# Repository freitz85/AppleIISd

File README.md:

# AppleIISd

SD card based ProFile replacement for enhanced Apple IIe and IIgs computers

The **AppleIISd** is a SD card based replaced for the ProFile harddrive. In contrast to other SD card based devices, this card does not replace a Disk II drive. Data is saved directly onto the SD card, not via images on a FAT system, like on other cards. The SD card is accessable with [CiderPress](http://a2ciderpress.com/).

A Xilinx CPLD is used as a SPI controller and translates, together with the ROM driver, SD card data to/from the Apple IIe. The VHDL source is based on [SPI65/B](http://www.6502.org/users/andre/spi65b) by André Fachat.

The assembler sources are written for CC65. The [schematics](Binary/AppleIISd.pdf) are available as PDF.

## Features

* works with ProDOS and GS/OS
* up to 128MB storage space (4x 65535 blocks)
* ProDOS and Smartport driver in ROM
* Firmware update from ProDOS
* Auto boot
* Access LED
* Card detect and write protect sensing
* Skip boot when Open-Apple key is pressed

## Requirements

The AppleIISd requires an enhanced IIe or IIgs computer. The ROM code uses some 65c02 opcodes and will therefore not work on a II, II+ or unenhanced IIe. It has been tested in the following combinations:

* Apple IIgs Rom 01, GS/OS 6.0.4
* Apple IIgs Rom 01, Prodos 2.4.1
* Apple IIgs Rom 01, Prodos 1.9
* Apple IIe enhanced, 128k, Prodos 2.4.1
* Apple IIe enhanced, 128k, Prodos 1.9
* Apple IIe enhanced, 64k, Prodos 1.9

## Binary distribution

The following files in [Binary/](Binary) have been provided to eliminate the need to compile assembler or VHDL sources.

| File | Purpose |
| ---- | ------- |
| AppleIISd_xx44.jed | CPLD bitfiles for PC44 and VQ44 formfactors |
| AppleIISd.bin | 2k Firmware binary for EPROM |
| AppleIISd.hex | Same as above in INTEL-HEX format |
| AppleIISd.bom.txt | BOM for the board |
| AppleIISd.pdf | Schematic and layout |
| Flasher.bin | Flasher program ProDOS binary |
| Flasher.dsk | Complete ProDOS disk image with Flasher.bin and AppleIISd.bin |
| Gerber_Vx.x.zip | Gerber files for different hw revisions |

## Smartport drive remapping

The AppleIISd features Smartport drivers in ROM to provide more than two drives in both GS/OS and ProDOS.

As ProDOS supports only two drives per slot, additional drives on a Smartport device are mapped to 'phantom slots'. Version prior to version 2 supported only the remapping of drives when the card was in slot 5. Starting with version 2, the remapping seems to work on all slots. The following list shows the assignments as slot/drive, when no other devices are attached:

* Slot 7: 7/1, 7/2, 4/1, 4/2
* Slot 6: 6/1, 6/2, 4/1, 4/1
* Slot 5: 5/1, 5/2, 2/1, 2/1
* Slot 4: 4/1, 4/2, 1/1, 1/2
* Slot 3: 80 col HW, not usable
* Slot 2: 2/1, 2/2, 4/1, 4/2
* Slot 1: 1/1, 1/2, 4/1, 4/2

When more devices are connected, things get a little confusing ;-)

## Building the sources

Be sure to have the newest version of CC65 (V2.16) and some kind of Make instaled, then type one of the following comands:

```bash
make                            # generate binaries
make OPTIONS=mapfile,listing    # generate mapfile and listing, too
make clean                      # delete binaries
```

Alternatively use the VisualStudio solution.

## Timing

The clock of the SPI bus *SCK* may be derived from either *Phi0* or the *7M* clock. Additionally, the divisor may be 2 to 8.

The following measurements were taken with the divisor set to 2, resulting in *fSCK* of 500kHz and 3.5MHz. Reading of a byte requires that a dummy byte is sent on the bus, before the answer can be read. Therefore the measurement is the time between sending the byte and receiving the answer. The measurement for reading of a whole 512 byte block includes the SD card commands to do so.

| Clock  | Byte   | Block  | Image                                             |
| -----: | -----: | -----: | ------------------------------------------------: |
| *Phi0* | 17.7µs | 28.8ms | [Byte](Images/Bus1.gif), [Block](Images/Spi1.png) |
| *7M*   | 3.9µs  | 15ms   | [Byte](Images/Bus2.gif), [Block](Images/Spi2.png) |

This shows that the required to read a single byte can be reduced significantly by increasing *fSCK* (as one might have guessed). Reading at 500kHz actualy requires NOPs to be inserted (or checking the TC bit in the STATUS register), while reading at 3.5MHz can be done immediately.

The time for reading a 512 byte block could *only* be halved, but there are for sure opportunities for optimization in the code surrounding the reading.

```asm
* single byte @ 500kHz
LDA #$FF
STA $C0C0
NOP
NOP
NOP
NOP
NOP
NOP
NOP
LDA $C0C0

* single byte @ 3.5MHz
LDA #$FF
STA $C0C0
LDA $C0C0
```

## Registers

The control registers of the *AppleIISd* are mapped to the usual I/O space at **$C0n0 - $C0n3**, where n is slot+8. All registers and bits are read/write, except where noted.

| Address | Function        | Default value |
| ------- | --------------- | ------------- |
| $C0n0   | DATA            | - |
| $C0n1   | **0:** PGMEN<br>**1:** -<br>**2:** ECE<br>**3:** -<br>**4:** FRX<br>**5:** BSY (R)<br>**6:** -<br>**7:** TC (R) | 0<br>0<br>0<br>0<br>0<br>0<br>0<br>0<br> |
| $C0n2   | unused          | $00 |
| $C0n3   | **0:** /SS<br>**1:** -<br>**2:** -<br>**3:** -<br>**4:** SDHC<br>**5:** WP (R)<br>**6:** CD (R)<br>**7:** INIT | 1<br>0<br>0<br>0<br>0<br>-<br>-<br>0 |

**DATA** SPI data register - Is used for both input and output. When the register is written to, the controller will output the byte on the SPI bus. When it is read from, it reflects the data that was received over the SPI bus.

**PGMEN** Program Enable - Enable programing of the internal firmware eeprom. Should be reset immediately after writing to the device.

**ECE** External Clock Enable - This bit enables the the external clock input to the SPI controller. In the *AppleIISd*, this effectively switches the SPI clock between 500kHz (ECE = 0) and 3.5MHz (ECE = 1).

**FRX** Fast Receive mode - When set to 1, fast receive mode triggers shifting upon reading or writing the SPI Data register. When set to 0, shifting is only triggered by writing the SPI data register.

**BSY** Busy - This bit is 1 as long as data is shifted out on the SPI bus. *BSY* is read-only.

**TC** Transfer Complete - This flag is set when the last bit has been shifted out onto the SPI bus and is cleared when *SPI data* is read.

**/SS** Slave select - Write 0 to this bit to select the SD card.

**SDHC** This bit is used by the initialization routine in firmware to signalize when a SDHC card was found. Do not write to manually.

**WP** Write Protect - This read-only bit is 0 when writing to the card is enabled by the switch on the card.

**CD** Card Detect - This read-only bit is 0 when a card is inserted.

**INIT** Initialized - This bit is set to 1 when the SD card has been initialized by the firmware. Do not write manually.

## TODOs

* Much more testing
* Enable more than 4 volumes under GS/OS
* Support for 6502 CPUs
* Support for CP/M

## Known Bugs

* Programs not startable from partitions 3 and 4 under ProDOS

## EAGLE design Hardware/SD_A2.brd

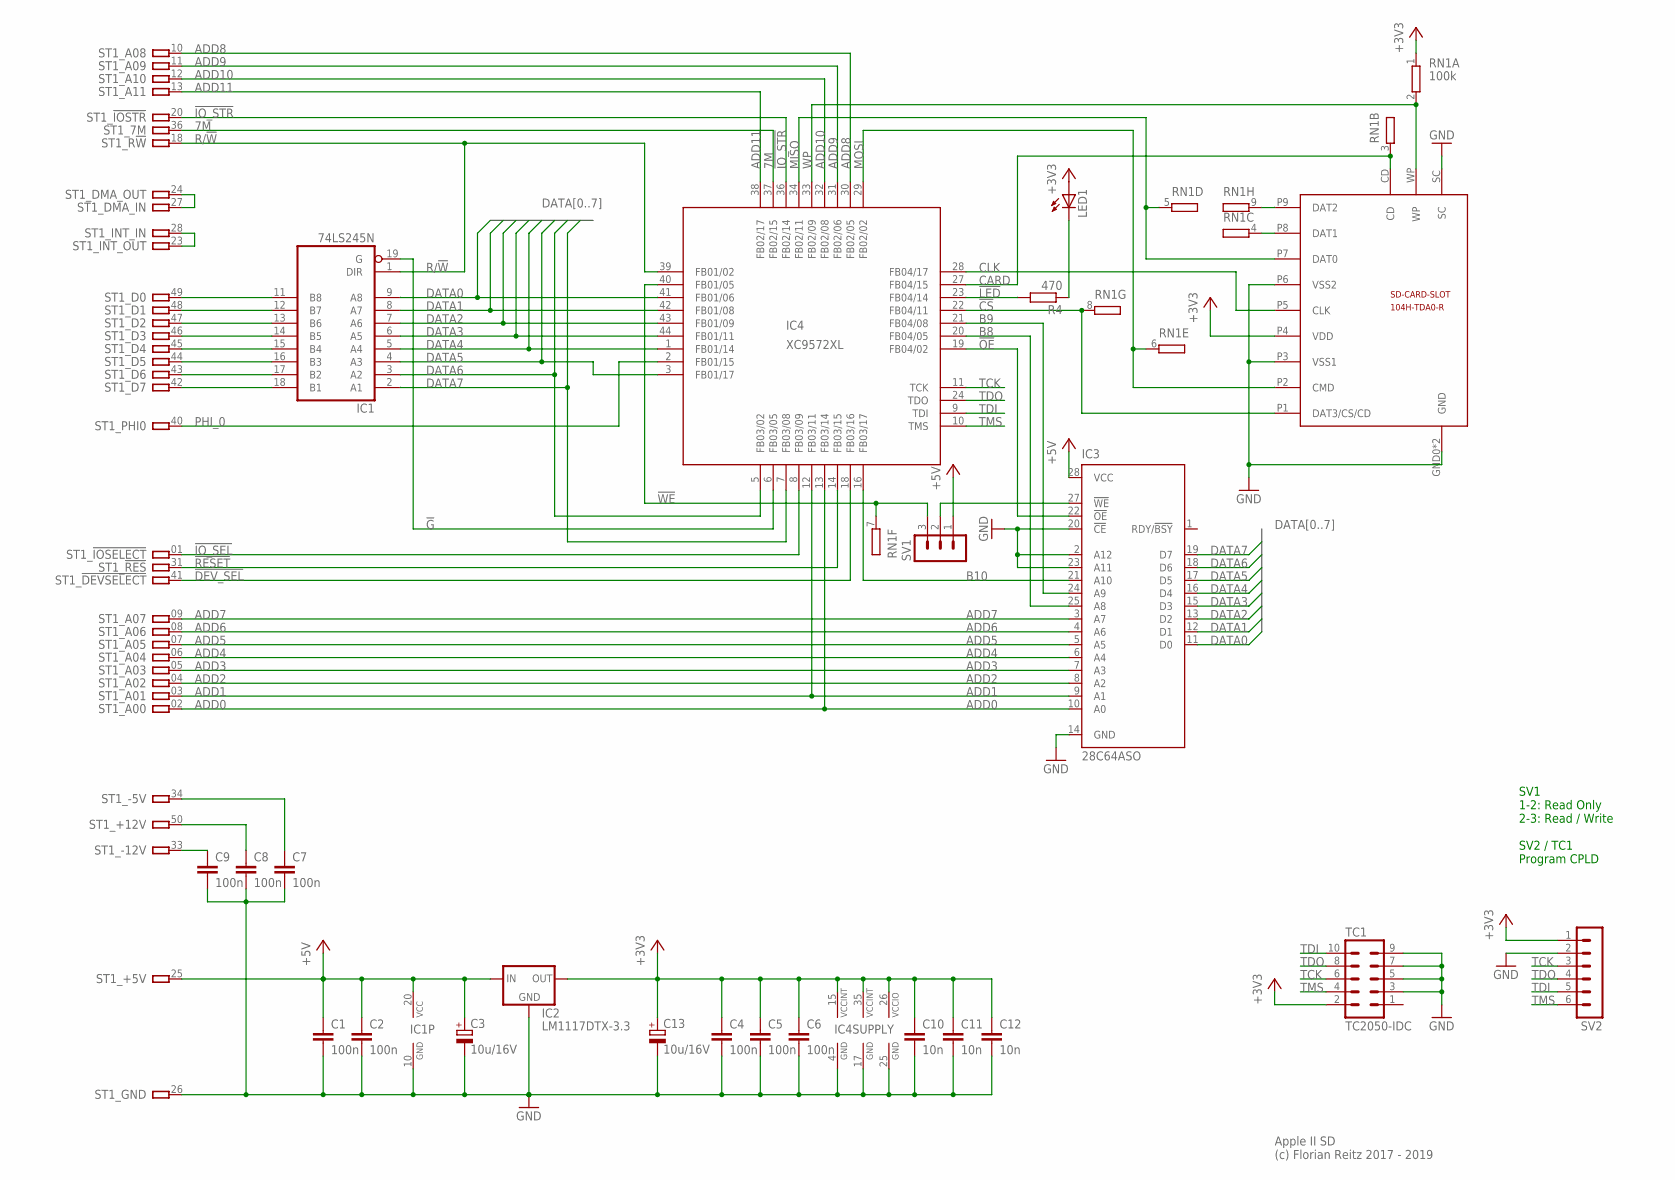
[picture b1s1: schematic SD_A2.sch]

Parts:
C1, C2, C4, C5, C6, C7, C8, C9: 100n; C0603K
C3, C13: 10u/16V; A/3216-18R
C10, C11, C12: 10n; C0603K
IC1: 74LS245N; DIL20
IC2: LM1117DTX-3.3; TO252
IC3: 28C64ASO; SO28W
IC4: XC9572XL; SQFP-S-10X10-44
LED1: LEDSQR2X5; LED2X5
R4: 470; R0603
RN1: 100k; SIL9
ST1: A2-50PINSLOT1-3; A2-50PIN-SL1-3
SV1: MA03-1
SV2: MA06-1
TC1: TC2050-IDC
U$2: 104H-TDA0-R

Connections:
7M: IC4.37 (FB02/15), ST1.36
!CS: IC4.22 (FB04/11), RN1.8 (2), U$2.P1 (DAT3/CS/CD)
!DEV_SEL: IC4.18 (FB03/16), ST1.41
!G: IC1.19 (G), IC4.6 (FB03/05)
!IO_SEL: IC4.8 (FB03/09), ST1.01
!IO_STR: IC4.36 (FB02/14), ST1.20
!LED: IC4.23 (FB04/14), R4.2
!OE: IC3.22 (!OE), IC4.19 (FB04/02)
!RESET: IC4.14 (FB03/15), ST1.31
!WE: IC4.40 (FB01/05), RN1.7 (2), SV1.3
+3V3: C4.1, C5.1, C6.1, C10.1, C11.1, C12.1, C13.+, IC2.TAB (OUT), IC4.15 (VCCINT), IC4.26 (VCCIO), IC4.35 (VCCINT), LED1.A, RN1.1, SV2.1, TC1.2, U$2.P4 (VDD)
+5V: C1.1, C2.1, C3.+, IC1.20 (VCC), IC2.2 (IN), IC3.28 (VCC), ST1.25, SV1.1
+12V: C8.1, ST1.50
-5V: C7.1, ST1.34
-12V: C9.1, ST1.33
ADD0: IC3.10 (A0), IC4.13 (FB03/14), ST1.02
ADD1: IC3.9 (A1), IC4.12 (FB03/11), ST1.03
ADD2: IC3.8 (A2), ST1.04
ADD3: IC3.7 (A3), ST1.05
ADD4: IC3.6 (A4), ST1.06
ADD5: IC3.5 (A5), ST1.07
ADD6: IC3.4 (A6), ST1.08
ADD7: IC3.3 (A7), ST1.09
ADD8: IC4.30 (FB02/05), ST1.10
ADD9: IC4.31 (FB02/06), ST1.11
ADD10: IC4.32 (FB02/08), ST1.12
ADD11: IC4.38 (FB02/17), ST1.13
B8: IC3.25 (A8), IC4.20 (FB04/05)
B9: IC3.24 (A9), IC4.21 (FB04/08)
B10: IC3.21 (A10), IC4.16 (FB03/17)
CARD: IC4.27 (FB04/15), RN1.3 (2), U$2.CD
CLK: IC4.28 (FB04/17), U$2.P5 (CLK)
D0: IC1.11 (B8), ST1.49
D1: IC1.12 (B7), ST1.48
D2: IC1.13 (B6), ST1.47
D3: IC1.14 (B5), ST1.46
D4: IC1.15 (B4), ST1.45
D5: IC1.16 (B3), ST1.44
D6: IC1.17 (B2), ST1.43
D7: IC1.18 (B1), ST1.42
DAT2: RN1.9 (2), U$2.P9 (DAT2)
DATA0: IC1.9 (A8), IC3.11 (D0), IC4.41 (FB01/06)
DATA1: IC1.8 (A7), IC3.12 (D1), IC4.42 (FB01/08)
DATA2: IC1.7 (A6), IC3.13 (D2), IC4.43 (FB01/09)
DATA3: IC1.6 (A5), IC3.15 (D3), IC4.44 (FB01/11)
DATA4: IC1.5 (A4), IC3.16 (D4), IC4.1 (FB01/14)
DATA5: IC1.4 (A3), IC3.17 (D5), IC4.3 (FB01/17)
DATA6: IC1.3 (A2), IC3.18 (D6), IC4.5 (FB03/02)
DATA7: IC1.2 (A1), IC3.19 (D7), IC4.7 (FB03/08)
DMA: ST1.24, ST1.27
GND: C1.2, C2.2, C3.-, C4.2, C5.2, C6.2, C7.2, C8.2, C9.2, C10.2, C11.2, C12.2, C13.-, IC1.10 (GND), IC2.1 (GND), IC3.2 (A12), IC3.14 (GND), IC3.20 (!CE), IC3.23 (A11), IC4.4 (GND), IC4.17 (GND), IC4.25 (GND), ST1.26, SV2.2, TC1.3, TC1.5, TC1.7, TC1.9, U$2.GND0 (GND), U$2.GND1 (GND), U$2.P3 (VSS1), U$2.P6 (VSS2), U$2.SC
INT: ST1.23, ST1.28
MISO: IC4.34 (FB02/11), RN1.5 (2), U$2.P7 (DAT0)
MOSI: IC4.29 (FB02/02), RN1.6 (2), U$2.P2 (CMD)
unnamed: IC3.27 (!WE), SV1.2
unnamed: RN1.4 (2), U$2.P8 (DAT1)
unnamed: LED1.K (C), R4.1
PHI_0: IC4.2 (FB01/15), ST1.40
R/!W: IC1.1 (DIR), IC4.39 (FB01/02), ST1.18
TCK: IC4.11 (TCK), SV2.3, TC1.6
TDI: IC4.9 (TDI), SV2.5, TC1.10
TDO: IC4.24 (TDO), SV2.4, TC1.8
TMS: IC4.10 (TMS), SV2.6, TC1.4
WP: IC4.33 (FB02/09), RN1.2, U$2.WP

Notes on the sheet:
Apple II SD (c) Florian Reitz 2017 - 2019
SV1 1-2: Read Only 2-3: Read / Write SV2 / TC1 Program CPLD

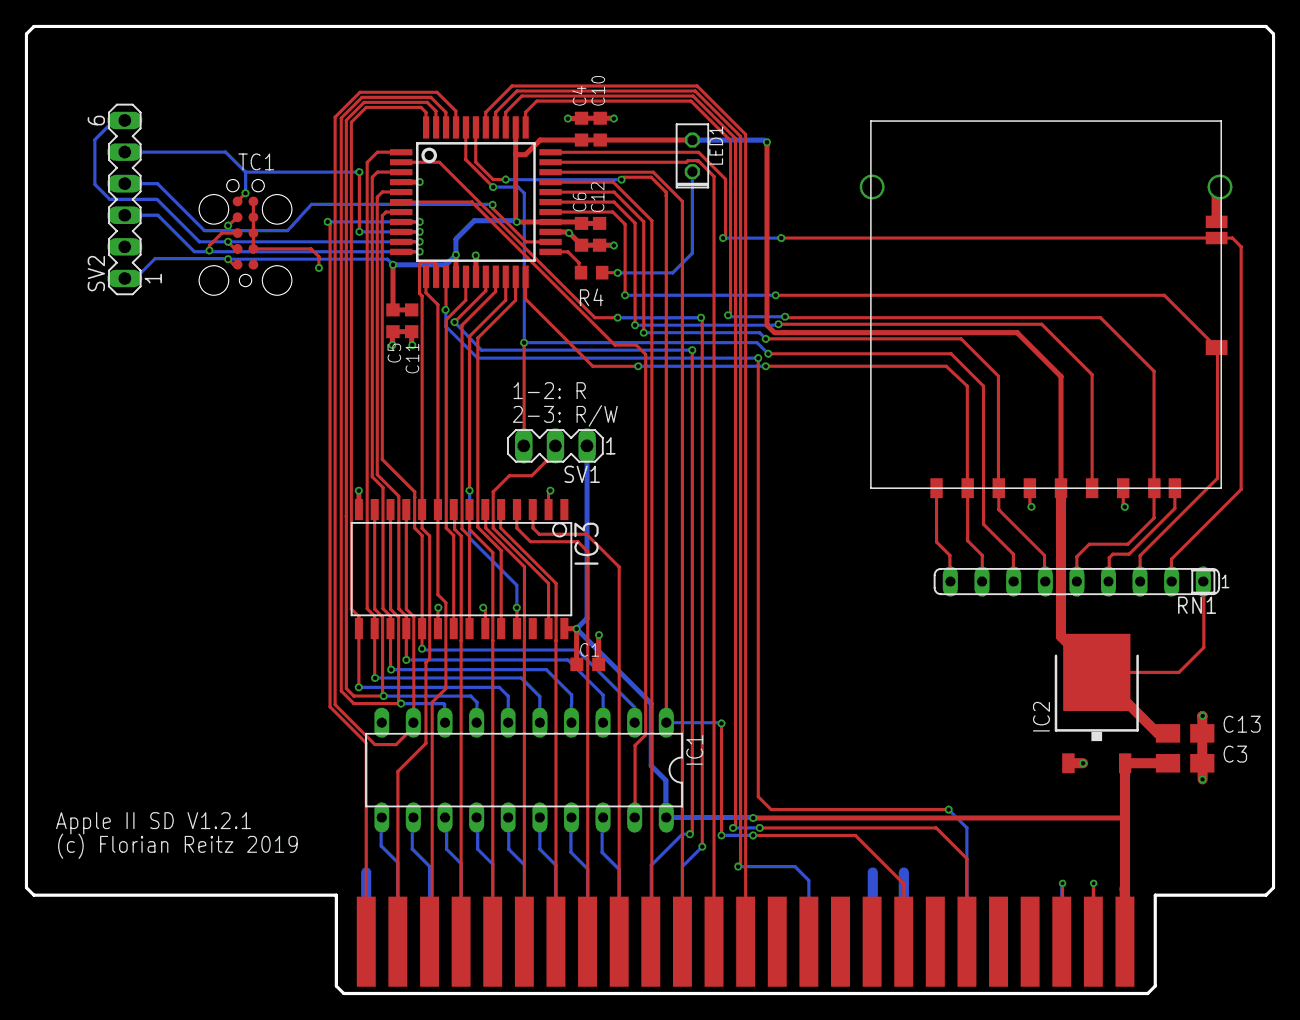
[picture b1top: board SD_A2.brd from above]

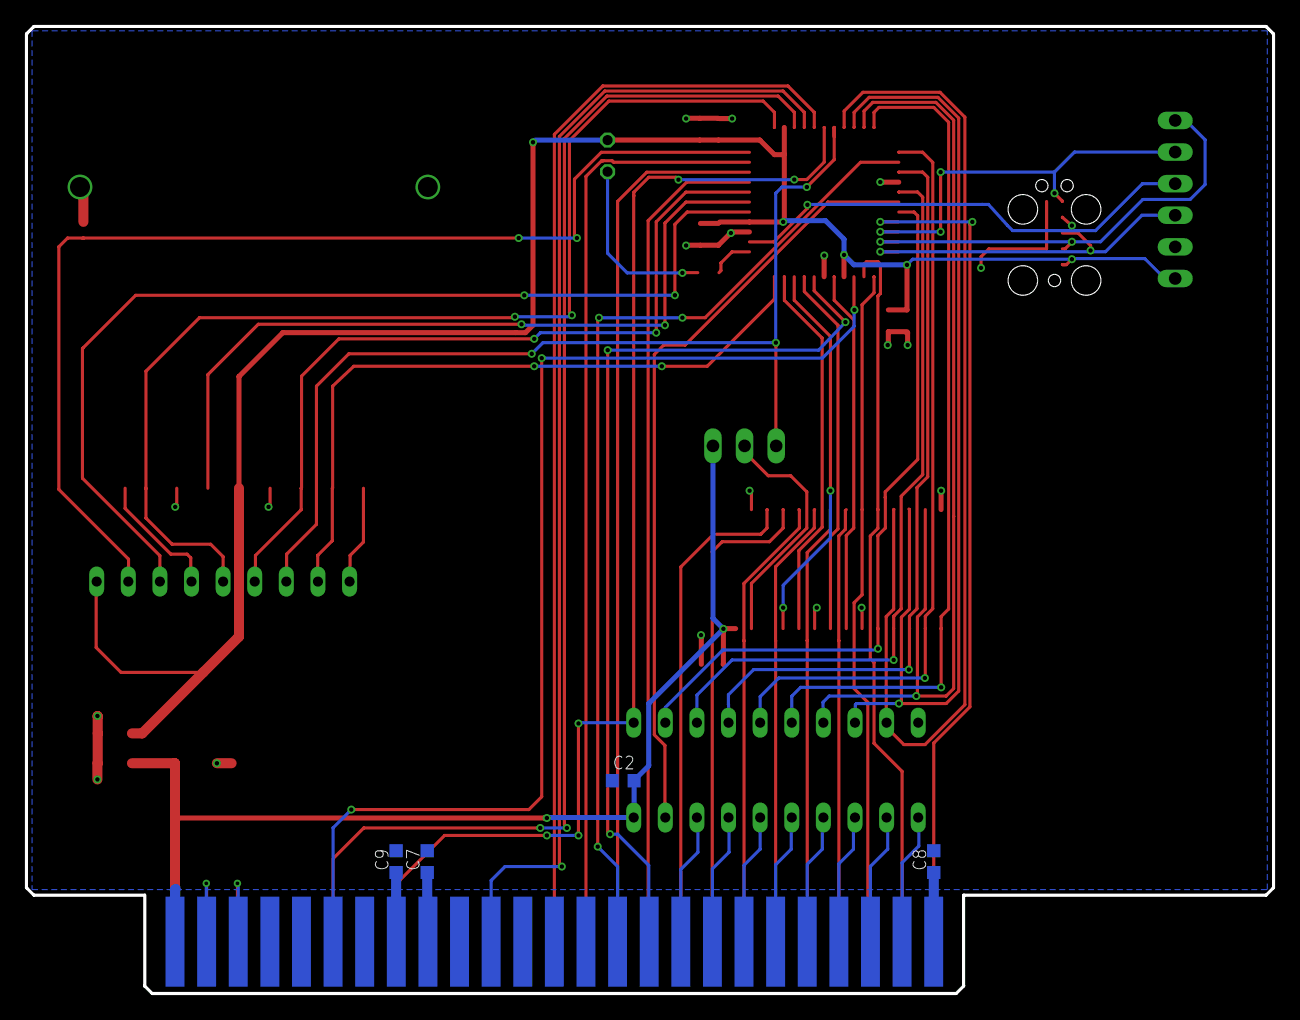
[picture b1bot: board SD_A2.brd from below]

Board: 2 copper layers, 100.2 x 77.7 mm, 25 parts (4 on the bottom side), 64 nets.

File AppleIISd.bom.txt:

Qty Value           Device            Package         Parts                          Description                                             
1                   LEDSQR2X5         LED2X5          LED1                           LED                                                     
1                   MA03-1            MA03-1          SV1                            PIN HEADER                                              
1                   MA06-1            MA06-1          SV2                            PIN HEADER                                              
1   100k            GE08R             SIL9            RN1                            SIL RESISTOR                                            
8   100n            C-EUC0603K        C0603K          C1, C2, C4, C5, C6, C7, C8, C9 CAPACITOR, European symbol                              
1   104H-TDA0-R     104H-TDA0-R       104H-TDA0-R     U$2                            SD Card Socket
3   10n             C-EUC0603K        C0603K          C10, C11, C12                  CAPACITOR, European symbol                              
2   10u/16V         CPOL-EUA/3216-18R A/3216-18R      C3, C13                        POLARIZED CAPACITOR, European symbol                    
1   28C64ASO        28C64ASO          SO28W           IC3                            CMOS EEPROM                                             
1   470             R-EU_R0603        R0603           R4                             RESISTOR, European symbol                               
1   74LS245N        74LS245N          DIL20           IC1                            Octal BUS TRANSCEIVER, 3-state                          
1   LM1117DTX-3.3   LM1117DTX-3.3     TO252           IC2                                                                                    
1   XC9572XL        XC9572_S44VQFP    SQFP-S-10X10-44 IC4

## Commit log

2017-05-06 files added
2017-05-06 additional misos and int removed
2017-07-05 folder structure added
2017-07-05 address decoder added
2017-07-05 removed unnecessary Xilinx files
2017-07-05 File rename
2017-07-05 ignored Xilinx files
2017-07-05 .gitignore
2017-07-05 Address decoding corrected
2017-07-05 Pinning changed
2017-07-05 signal rename and pinning
2017-07-05 !CE on GND
2017-07-09 Pin changes, libraries added
2017-07-09 Pin changes
2017-07-09 Merlin 8 source added
2017-07-10 test
2017-07-11 Datasheets added
2017-07-12 R and C changed to SMD
2017-07-15 Source and Listing updated to ROM location
2017-07-16 Debug flags added, block and command sequences moved to subroutine
2017-07-16 Fixed bug in Write Block
2017-07-18 - Gerber files
2017-08-11 Several fixes, binary and srec files added
2017-08-11 Small changes on board
2017-08-12 several fixes, not completely booting
2017-08-13 Fix for line ending
2017-08-13 Fix for crc after read command
2017-08-24 Schematic as PDF and BOM
2017-08-26 Images added
2017-08-26 Code updated for Merlin32
2017-08-26 7MHz clock used, read/write improved
    reverted to Merlin-8
2017-08-27 inited signal added to cpld
2017-08-27 inited flag in fpga
2017-08-30 inited flag is removed when card is ejected
2017-09-03 formatting
2017-09-05 misc datasheets added
2017-09-09 Support for second partition, card detect and write protect added
2017-09-10 Reset inited on card remove
2017-10-03 Check for init failure
2017-10-05 PLCC44 Socket Pinout
2017-10-05 several fixes tried
2017-10-08 test with clocked input buffers
2017-10-09 Timing diagram added
2017-10-09 Top level in VHDL
2017-10-09 Removed BUFG constraint warnings
2017-10-09 Test bench
2017-10-09 Test bench added
2017-10-10 Test bench worst and best case timings
2017-10-10 Synthesis guards for debug signals
2017-10-10 AddressDecoder in VHDL
2017-10-10 Rename files
2017-10-10 Spi simulation working
2017-10-12 AddressDecoder testbench
2017-10-13 Fixes according to IIgs Tech Note #68
2017-10-15 Test routine added
2017-10-15 More VDHL tests added
2017-10-16 IRQ Pin removed, A11 added
2017-10-16 Test for old AddressDecoder
2017-10-16 New address decoding
2017-10-16 Hex file for new address mapping
2017-10-22 Linear addressing from C700, test code added to ram
2017-10-23 Linear addressing from Cn00
2017-11-01 Save and restore ZP locations
    Shorter read write loops
2017-11-01 SPI Mode 3
2017-11-20 Load block 0 and 1 on boot
2017-11-25 SDHC flag added to CPLD
2017-11-25 Source updated for CC65
2017-11-25 VS2015 project added
2017-11-26 IIgs boot working!!!
2017-11-29 Boot verified for IIgs, IIe 128k and IIe 64k
2017-11-30 Schematic updated
2017-11-30 Change in makefile and folder structure
2017-11-30 Skip boot added
2017-12-01 README.md updated
2017-12-01 Schematic PDF updated
2017-12-05 Gerber for V1.1
2017-12-12 Helper and include files added
2017-12-16 Fix for non-SDHC SDV2
2017-12-17 Updated to V1.1
2017-12-17 ProDOS functions moved to separate file
    Debug functions removed
2017-12-19 Test with phantom slots
2017-12-23 ProDOS image for testing added
2018-05-17 Smartport.s added
2018-05-17 Error codes added
2018-05-17 ProDOS jump table moved
2018-05-17 Save zeropage in loop
2018-05-22 Prepared for Smartport
2018-05-23 Smartport dispatcher added
2018-05-23 All Smartport functions except Status and Control added
2018-05-24 Smartport Control added
2018-05-24 Status command added
2018-05-25 Timing overview added
2018-05-28 Smartport seems to work
2018-05-29 Status00 call updated
2018-07-07 Nasty bug in Status call fixed
2018-09-28 Fix in ProDOS write
2018-10-10 Added waiting for card ready.
2019-03-03 Timing diagrams
2019-03-03 NWE signal added, not tested
2019-03-03 NWE added to schematic and layout
2019-03-03 LED removed from AddressDecoder
2019-03-03 Expected results added to AddressDecoder simulation
2019-03-03 AddressDecoder verified in simulation
2019-03-03 Program enable added and verified
2019-03-03 Tag Connect added
2019-03-03 EEPROM as SMD
2019-03-03 Resistor network added
2019-03-03 Trace width 0.254
2019-03-03 Keepout for Tag Connect
2019-03-03 Rename in AII connector
2019-03-03 Firmware folder added
2019-03-03 Flasher project added
2019-03-03 First flasher version, untested
2019-03-04 typedefs
2019-03-05 Fixes for console output
2019-03-05 Verification added
2019-03-07 Flasher working
2019-03-09 Schematic as Eagle V7 file
2019-03-10 BOM and schematic as PDF
2019-03-16 XC9572XL library with VQFP44 package added
2019-03-17 CPLD changed to VQFP package
2019-03-17 VHDL for VQFP and PLCC packages
2019-03-17 Asserts for simulation
2019-03-21 LM317 replaced with LM1117
2019-04-10 Gerber for V1.2
2019-05-27 Registers.vhd added
2019-06-02 Fix in VQ44 pinning
2019-06-04 Pullup on /WE added
2019-06-04 Longer slot pins
2019-06-17 Register description
2019-08-10 Changes for 6502 cpu
2019-11-08 Datasheets
2019-11-10 Translation bugs
2019-11-10 Readme update
2019-11-19 R/W jumper re-added
2019-11-19 Binary folder added
2019-11-22 Gerber V1.2.1
2020-02-09 SMD board image added
2020-02-09 Test with 8 drives for ProDOS 2.5
2020-06-04 Erase added to flasher
2020-06-04 Wait for writecycle
2020-06-04 Fix for unintended PGMEN usage
2020-06-04 Local replacement for KNOWNRTS
2020-08-15 Check card status in ProDOS commands
2020-08-31 Volatile qualifiers added
2020-10-01 Verification separated
2020-10-03 Use array access instead of pointers
2020-10-03 make_image.sh improved
2020-12-21 Force enable EXT_ROM
2021-02-20 Release V1.2.2
2021-08-24 Fix in INIT
2021-08-24 Set DSNUMBER on boot
2021-08-24 Replace BIT with LDA
